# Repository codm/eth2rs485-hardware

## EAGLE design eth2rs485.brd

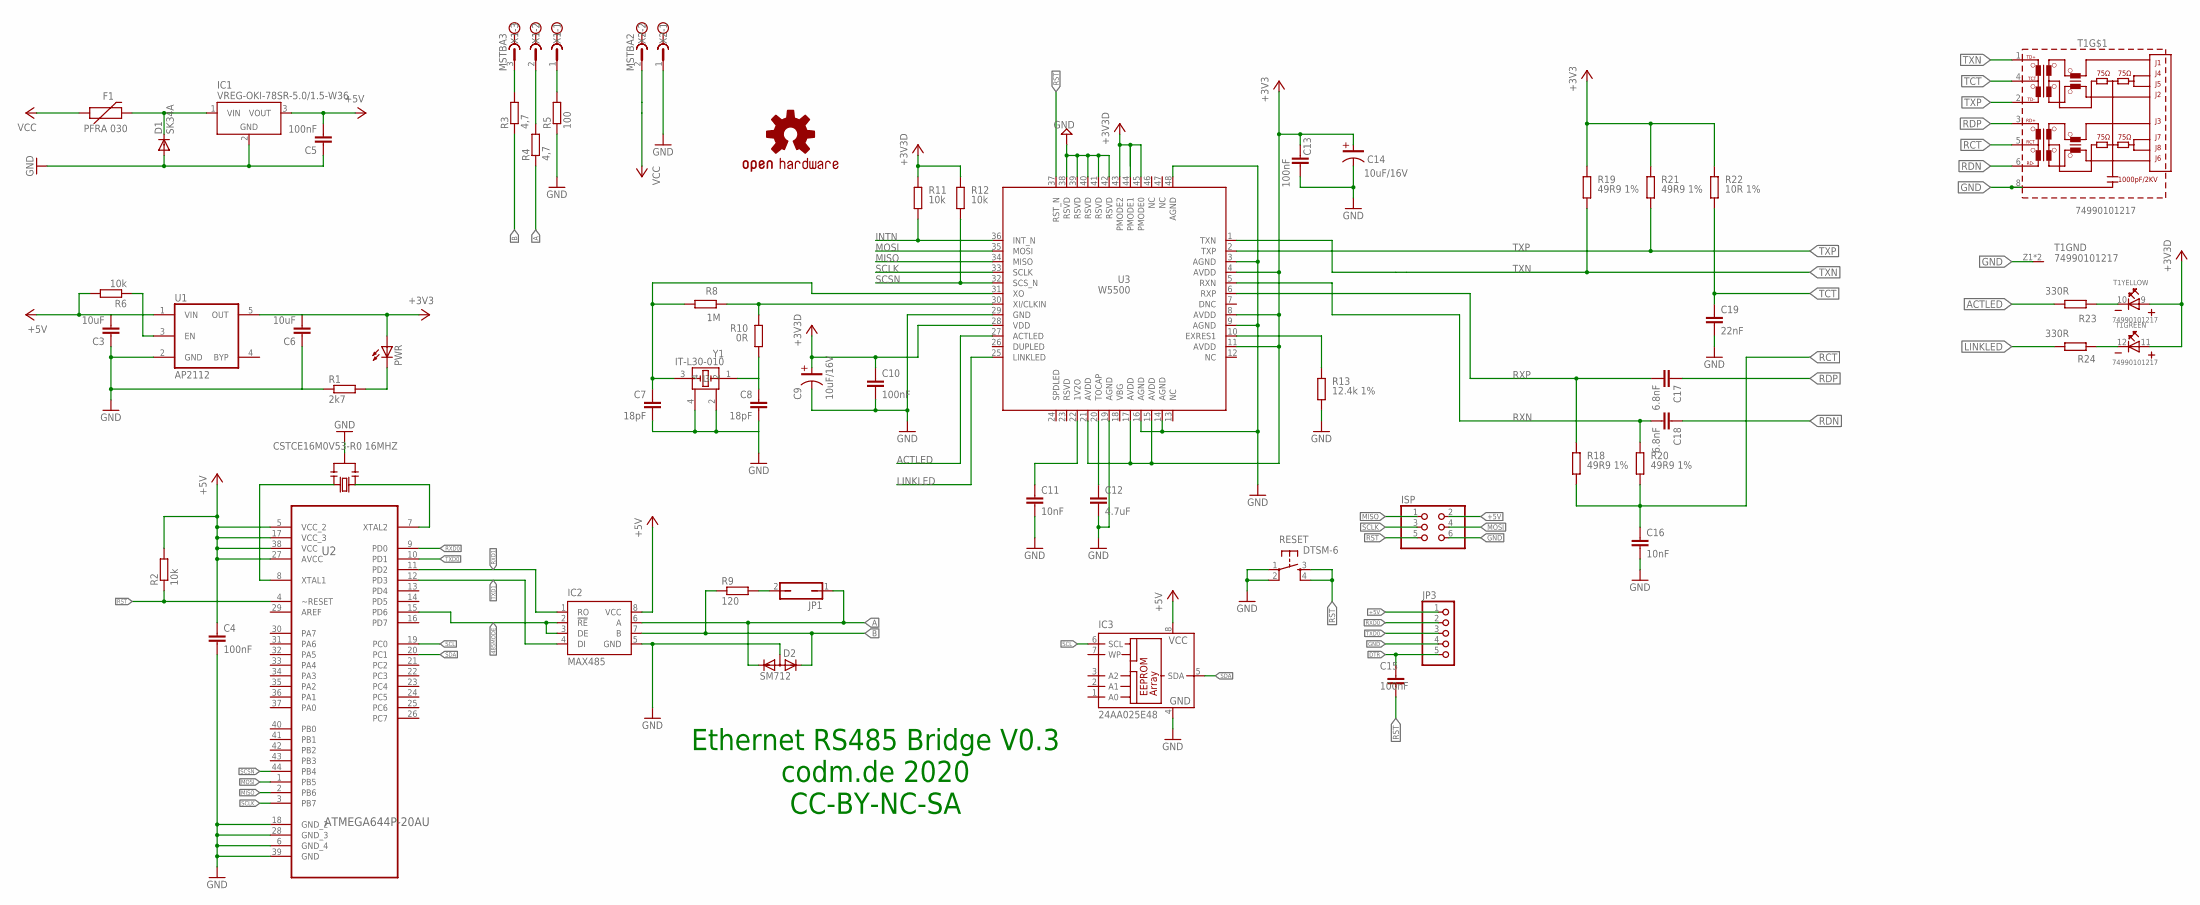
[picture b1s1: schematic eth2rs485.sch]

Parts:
C3, C6: 10uF; C0805
C4, C5, C10, C13, C15: 100nF; C0805
C7, C8: 18pF; C0805
C9, C14: 10uF/16V; C-3216(TANTAL)
C11, C16: 10nF; C0805
C12: 4.7uF; C0805
C17, C18: 6.8nF; C0805
C19: 22nF; C0805
D1: SK34A; DO214AC
D2: SM712; SOT23
F1: PFRA 030; PTH
IC1: VREG-OKI-78SR-5.0/1.5-W36; OKI-78SR
IC2: MAX485; SOIC8
IC3: 24AA025E48; SO-08
ISP: PINHD-2X3; 2X03
JP1: JP1Q; JP1
JP3: PINHD-1X5; 1X05
LOGO1: OSHW-LOGOM; OSHW-LOGO-M
PWR: LEDCHIP-LED0805; CHIP-LED0805
R1: 2k7; R0805
R2, R6, R11, R12: 10k; R0805
R3, R4: 4,7; R0805
R5: 100; R0805
R8: 1M; R0805
R9: 120; R0805
R10: 0R; R0805
R13: 12.4k 1%; R0805
R18, R19, R20, R21: 49R9 1%; R0805
R22: 10R 1%; R0805
R23, R24: 330R; R0805
RESET: DTSM-6
T1: 74990101217; 74990111217
U1: AP2112; SOT23-5
U2: ATMEGA644P-20AU; QFP80P1200X1200X120-44N
U3: W5500
X1: MSTBA3
X2: MSTBA2
Y1: IT-L30-010
Y2: CSTCE16M0V53-R0 16MHZ; RESONATOR

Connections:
485MODE: IC2.2 (!RE), IC2.3 (DE), U2.15 (PD6)
+3V3: C6.2, C9.1, C10.1, C13.1, C14.1, PWR.A, R11.2, R12.2, R19.2, R21.2, R22.2, T1.9 (A), T1.11 (A), U1.5 (OUT), U3.4 (AVDD), U3.8 (AVDD), U3.11 (AVDD), U3.15 (AVDD), U3.17 (AVDD), U3.21 (AVDD), U3.28 (VDD), U3.43 (PMODE2), U3.44 (PMODE1), U3.45 (PMODE0)
+5V: C3.2, C4.1, C5.2, IC1.3 (VOUT), IC2.8 (VCC), IC3.8 (VCC), ISP.2, JP3.1, R2.2, R6.2, U1.1 (VIN), U2.5 (VCC_2), U2.17 (VCC_3), U2.27 (AVCC), U2.38 (VCC)
A: D2.1 (K1), IC2.6 (A), JP1.1, R4.1
ACTLED: R23.1, U3.27 (ACTLED)
B: D2.2 (K2), IC2.7 (B), R3.1, R9.1
DTR: C15.1, JP3.5
GND: C3.1, C4.2, C5.1, C6.1, C7.2, C8.2, C9.2, C10.2, C11.2, C12.2, C13.2, C14.2, C16.2, C19.2, D1.A, D2.3 (A), IC1.2 (GND), IC2.5 (GND), IC3.4 (GND), ISP.6, JP3.4, R1.1, R5.1, R13.1, RESET.1, RESET.2, T1.8, T1.Z1 (GND), T1.Z2 (GND), U1.2 (GND), U2.6 (GND_4), U2.18 (GND_2), U2.28 (GND_3), U2.39 (GND), U3.3 (AGND), U3.9 (AGND), U3.14 (AGND), U3.16 (AGND), U3.19 (AGND), U3.29 (GND), U3.38 (RSVD), U3.39 (RSVD), U3.40 (RSVD), U3.41 (RSVD), U3.42 (RSVD), U3.48 (AGND), X2.1, Y1.2, Y1.4, Y2.2
INTN: R11.1, U3.36 (INT_N)
LINKLED: R24.1, U3.25 (LINKLED)
MISO: ISP.1, U2.2 (PB6), U3.34 (MISO)
MOSI: ISP.4, U2.1 (PB5), U3.35 (MOSI)
unnamed: C12.1, U3.20 (TOCAP)
unnamed: R6.1, U1.3 (EN)
unnamed: R5.2, X1.1
unnamed: R3.2, X1.3
unnamed: R4.2, X1.2
unnamed: PWR.C, R1.2
unnamed: D1.C, F1.P$2 (2), IC1.1 (VIN)
unnamed: R8.2, R10.2, U3.30 (XI/CLKIN)
unnamed: JP1.2, R9.2
unnamed: C11.1, U3.22 (1V2O)
unnamed: R13.2, U3.10 (EXRES1)
unnamed: C7.1, R8.1, U3.31 (XO), Y1.3
unnamed: C8.1, R10.1, Y1.1
unnamed: R23.2, T1.10 (K)
unnamed: R24.2, T1.12 (K)
RCT: C16.1, R18.1, R20.1, T1.5 (RCT)
RDN: C18.1, T1.6 (RD-)
RDP: C17.1, T1.3 (RD+)
RST: C15.2, ISP.5, R2.1, RESET.3, RESET.4, U2.4 (~RESET), U3.37 (RST_N)
RXD0: JP3.2, U2.9 (PD0)
RXD1: IC2.1 (RO), U2.11 (PD2)
RXN: C18.2, R20.2, U3.5 (RXN)
RXP: C17.2, R18.2, U3.6 (RXP)
SCL: IC3.6 (SCL), U2.19 (PC0)
SCLK: ISP.3, U2.3 (PB7), U3.33 (SCLK)
SCSN: R12.1, U2.44 (PB4), U3.32 (SCS_N)
SDA: IC3.5 (SDA), U2.20 (PC1)
TCT: C19.1, R22.1, T1.4 (TCT)
TXD0: JP3.3, U2.10 (PD1)
TXD1: IC2.4 (DI), U2.12 (PD3)
TXN: R19.1, T1.1 (TD+), U3.1 (TXN)
TXP: R21.1, T1.2 (TD-), U3.2 (TXP)
VCC: F1.P$1 (1), X2.2
XTAL1: U2.8 (XTAL1), Y2.3
XTAL2: U2.7 (XTAL2), Y2.1

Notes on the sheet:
Ethernet RS485 Bridge V0.3 codm.de 2020 CC-BY-NC-SA

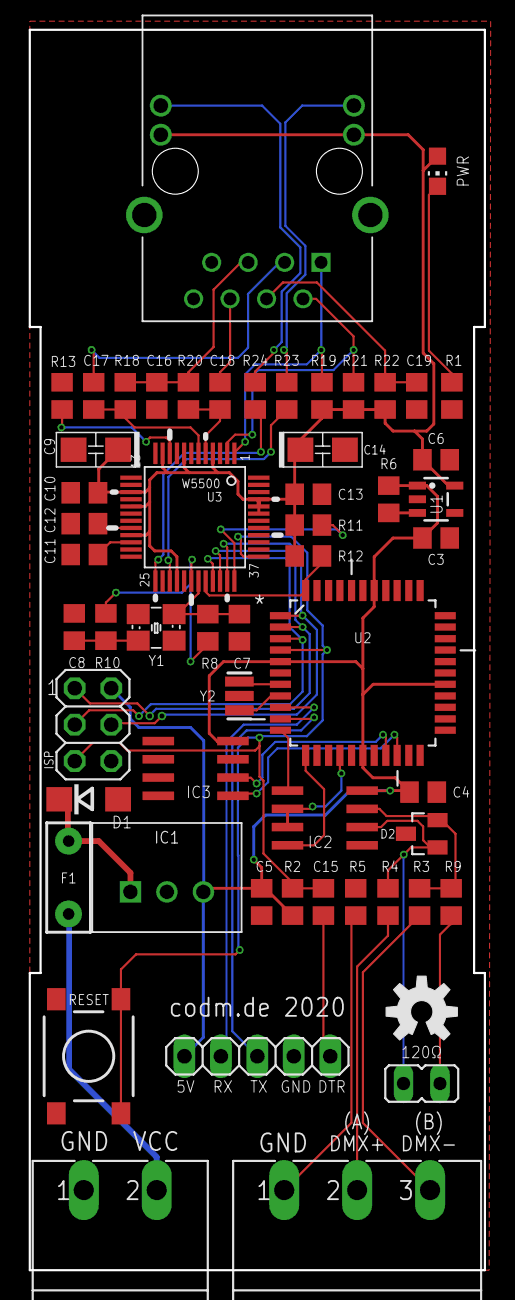
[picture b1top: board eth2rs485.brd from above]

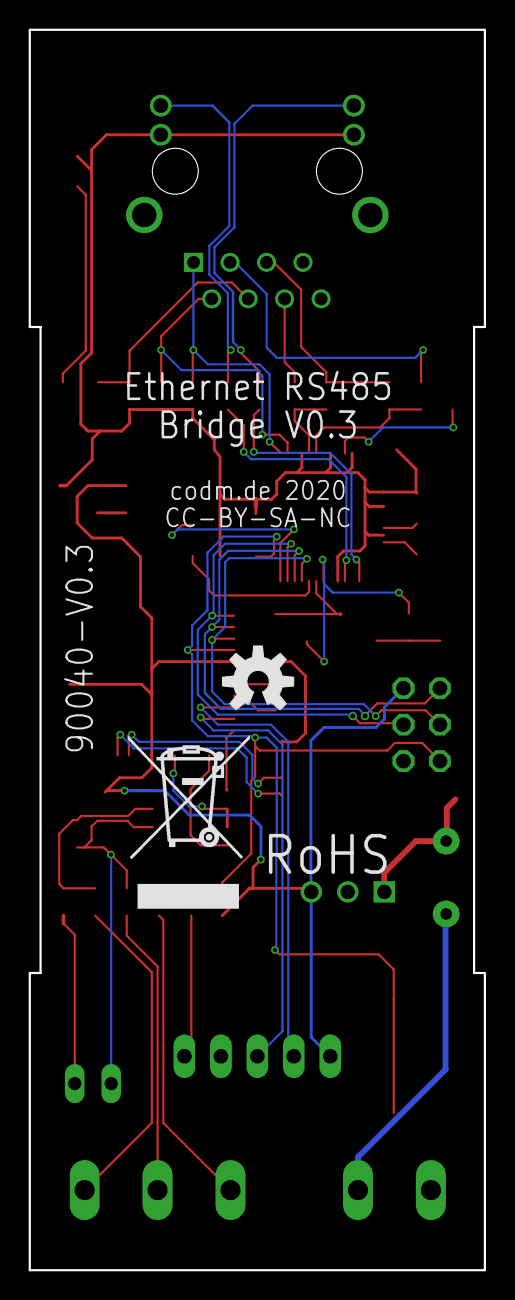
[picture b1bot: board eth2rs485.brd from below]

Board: 2 copper layers, 31.7 x 86.4 mm, 58 parts (2 on the bottom side), 47 nets.

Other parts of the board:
LOGO2: OSHW-LOGOM; OSHW-LOGO-M
U$3: WEEE-LOGO-8MM

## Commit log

2019-01-29 fixed type
2019-01-29 fixed typo
2019-01-29 swapped 328p for 644p
2019-02-15 finished routing for prototype
2019-02-15 typo
2020-03-02 atmega 644 working (hopefully)
2020-12-10 added sch pdf, minor changes brd

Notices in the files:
eth2rs485.brd:
CC-BY-SA-NC
parts and their libraries:
SignalCommunications: Copyright: Würth Elektronik
SparkFun-Aesthetics: Licensing: Creative Commons ShareAlike 4.0 International - https://creativecommons.org/licenses/by-sa/4.0
